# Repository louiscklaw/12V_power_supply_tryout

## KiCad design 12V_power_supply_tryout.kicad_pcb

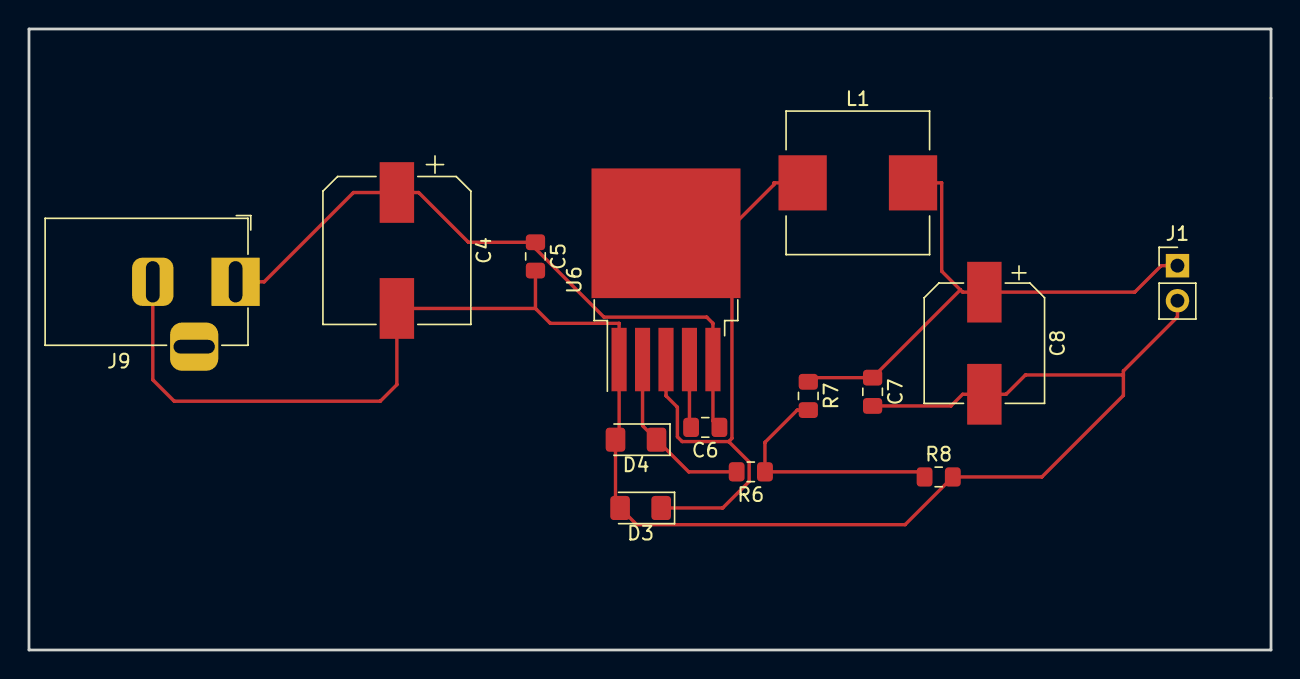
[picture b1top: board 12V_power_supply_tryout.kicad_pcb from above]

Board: 2 copper layers, 90.0 x 45.0 mm, 14 parts (0 on the bottom side), 7 nets.

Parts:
C4: CP220uf,50V; CP_Elec_10x10.5
C5, C6, C7: C105,0805; C_0805_2012Metric_Pad1.15x1.40mm_HandSolder
C8: CP330uf,25V; CP_Elec_8x10.5
D3: SD_SS510; D_1206_3216Metric_Pad1.42x1.75mm_HandSolder
D4: SD_1N5817_SS12; D_1206_3216Metric_Pad1.42x1.75mm_HandSolder
J1: Conn_01x02; PinHeader_1x02_P2.54mm_Vertical
J9: Barrel_Jack_Switch; BarrelJack_Horizontal
L1: L_47UH,5A,1040; L_Wuerth_HCI-1040
R6: R103,0805; R_0805_2012Metric_Pad1.15x1.40mm_HandSolder
R7: R333,0805; R_0805_2012Metric_Pad1.15x1.40mm_HandSolder
R8: R332,0805; R_0805_2012Metric_Pad1.15x1.40mm_HandSolder
U6: XL4015; TO-263-5_TabPin3

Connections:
+12V: C7.1, C8.1, J1.1, L1.2, R7.1
+24V: C4.1, C5.1, C6.1, J9.1, U6.5
GND: C4.2, C5.2, C7.2, C8.2, D3.2, D4.2, J1.2, J9.2, R8.2, U6.1
unnamed: C6.2, U6.4
unnamed: D3.1, L1.1, U6.3
unnamed: D4.1, R6.2, U6.2
unnamed: R6.1, R7.2, R8.1

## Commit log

2018-12-04 update,
2020-05-05 ci: init travis build config,
2020-05-05 ci: init travis token,
2020-05-15 ci: update and test,
2020-05-15 ci: add export in travis.yml,
